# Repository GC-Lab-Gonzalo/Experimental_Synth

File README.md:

# Experimental Synth — Sintetizador de Madera

Sintetizador experimental de **GC Lab Chile**: una caja de madera con un teclado de 49 teclas reciclado de un Casio,
perillas, teclas mecánicas y LEDs RGB. Funciona con dos ESP32-S3 y tres placas de 180 × 75 mm diseñadas en KiCad 9.

| Placa | Qué hace |
|---|---|
| **Cerebro** | ESP32-S3, teclado (MCP23017), DAC PCM5102A, OLED, microSD, encoder EC11 y 8 LEDs WS2812B |
| **Control** | 8 perillas y 16 teclas leídas con 3 multiplexores CD74HC4051, más 16 LEDs WS2812B |
| **Placa 1** | Plantas y entorno: ESP32-S3, sensores ambientales, dos SHT40, radar HLK-LD2410C, DAC y pantalla |

## ⚠️ Fallos conocidos (corregidos en los archivos actuales)

**v6 → v6.1 (2026-11-24): huella de los LED WS2812B 6028 en espejo.**
En la revisión v6 de las placas **Cerebro** y **Control**, la huella del LED de montaje inverso
(`LED_WS2812B_6028_REV`) quedó en espejo respecto del componente real. GND y 5V caían en la diagonal equivocada,
así que el LED no calzaba en ninguna orientación. Afectó a los 24 LEDs.

- **Los archivos de este repositorio (v6.1) ya están corregidos.** La huella nueva `LED_WS2812B-6028_Inverso`
  (en `hardware/biblioteca/GCLab.pretty/`) se verificó contra la hoja de datos XINGLIGHT XL-6028RGBC-WS2812B
  (pág. 11, vista desde la lente) y contra la placa PercuSynth V2, que usa el mismo LED y funciona.
- La zona de los LED se re-ruteó en las dos placas. El DRC de KiCad da 0 errores y 0 conexiones pendientes,
  igual que antes. El orden de la cadena de LEDs no cambió, así que el firmware sirve tal cual.
- Cada LED tiene ahora un **triángulo de serigrafía junto al pad de GND**. La pata en punta del 6028
  (la de la esquina cortada) es GND. En la fila de abajo de la Control los LED van girados 180° respecto de
  los de arriba.
- **Si tienes placas v6 ya fabricadas:** suelda los LED mirando hacia atrás o corrige con puentes de cable
  esmaltado. No vuelvas a fabricar la v6: sus archivos no se publican aquí.

La Placa 1 no lleva estos LED y no cambió.

## Contenido

```
hardware/
  kicad/          Placas en KiCad 9 (cerebro_v6.1, control_v6.1, placa1_v4)
  fabricacion/    Un ZIP de Gerber + taladros por placa, listo para JLCPCB, y renders de frente y atrás
  biblioteca/     GCLab.pretty con la huella corregida del WS2812B 6028 inverso
firmware/         Sketches de Arduino para ESP32-S3 (pruebas por placa y los dos sintetizadores)
docs/
  PINOUT.md       Conexiones, pines del ESP32-S3, cable entre placas, teclado, LEDs y multiplexores
  montaje/        Diagramas de conexión del módulo MCP23017 con el teclado
```

## Fabricar

- Sube el ZIP de `hardware/fabricacion/<placa>/` tal cual. Son placas de 2 capas, de 180 × 75 mm.
- Las ventanas rectangulares de los LED son cortes de la placa (van en el contorno, capa Edge.Cuts).
- Compra el WS2812B 6028 en versión **de montaje inverso** («reverse mount»), por ejemplo el XINGLIGHT
  XL-6028RGBC-WS2812B. Uno común queda alumbrando hacia atrás.

## Antes de armar

- **5V del ESP32-S3 (Cerebro):** el DAC, los LEDs y el cable a la Control se alimentan del pin 5V del
  ESP32-S3-DevKitC-1. Muchas de esas placas traen ese pin desconectado hasta que se cierra un puente de soldadura
  (marcado IN-OUT o similar). Si nada de 5V prende, revisa ese puente.
- **Orientación del ESP32 en la Cerebro:** guíate por la serigrafía (pin 1 = 3V3). Para cables provisorios usa los
  pads rotulados de la placa (OLED, J3) y no cuentes pines del módulo.
- **Firmware de LEDs:** con el núcleo Arduino-ESP32 3.2.0, `Adafruit_NeoPixel` puede fallar al azar (los LED se
  apagan). `firmware/synth_ambiente_placa1/` maneja el RMT directo con la configuración en cero para evitarlo;
  `firmware/prueba_placa1/` todavía usa `Adafruit_NeoPixel`. Otra opción es usar el núcleo 3.3.x.
- Compila con «USB CDC On Boot: Enabled» y programa por el USB nativo del ESP32-S3.

## Licencia

Todo el contenido de este repositorio (placas, Gerber, huellas, firmware y documentación) está bajo la licencia
[Creative Commons Atribución-NoComercial-CompartirIgual 4.0 Internacional (CC BY-NC-SA 4.0)](LICENSE).

- **Puedes** usarlo, estudiarlo, modificarlo y fabricar placas para ti o para enseñar sin fines de lucro.
- **Debes** dar crédito a GC Lab Chile y enlazar este repositorio: `https://github.com/GC-Lab-Gonzalo/Experimental_Synth`.
- **No puedes** venderlo ni usarlo con fines comerciales (por ejemplo, vender placas, kits o instrumentos basados
  en este diseño, o cobrar talleres que lo usen) sin permiso escrito de GC Lab Chile.
- Si lo modificas y lo compartes, tiene que ser con esta misma licencia.

¿Te interesa un uso comercial? Escríbenos desde [gclabchile.com](https://www.gclabchile.com).

Copyright © 2026 GC Lab Chile.

---

Hecho en Chile por [GC Lab Chile](https://www.gclabchile.com): ingeniería electrónica, IA y artes creativas.

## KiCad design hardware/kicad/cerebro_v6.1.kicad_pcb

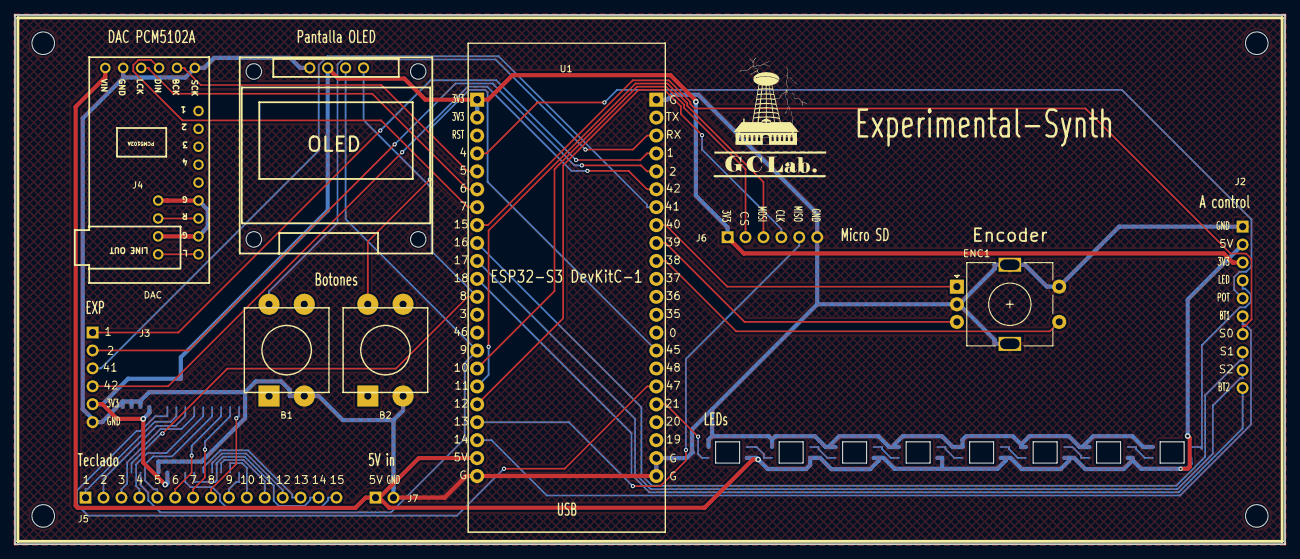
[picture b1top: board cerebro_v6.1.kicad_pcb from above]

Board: 2 copper layers, 180.0 x 75.0 mm, 26 parts (0 on the bottom side), 55 nets.

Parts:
B1, B2: TACT_12X12_PROTOSYNTH
C1: C0805
D1, D2, D3, D4, D5, D6, D7, D8: XL-6028RGBC-WS2812B; LED_WS2812B-6028_Inverso
DAC: PCM5102A
ENC1: EC11; RotaryEncoder_Alps_EC11E-Switch_Vertical_H20mm
Hole_gge700002: Hole_gge700002
Hole_gge700003: Hole_gge700003
Hole_gge700004: Hole_gge700004
Hole_gge700005: Hole_gge700005
J2: HDR_1X10
J3: HDR_1X6
J4: LINEOUT_1X4
J5: HDR_1X15
J6: MICROSD_3V3_1X6
J7: HDR_1X2
OLED: OLED-TH_OLED0.96-I2C
U1: ESP32-S3-DEVKITC-1
U3: SOIC28W_MCP23017

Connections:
3V3: C1.1, J2.3, J3.5, J6.1, OLED.4, U1.1, U1.2, U3.9, U3.18
5V: D1.3, D2.3, D3.3, D4.3, D5.3, D6.3, D7.3, D8.3, DAC.15, J2.2, J7.1, U1.21
AGND: DAC.6, DAC.8, J4.1, J4.3
BCK: DAC.11, U1.5
BL1: D1.4, D2.2
BL2: D2.4, D3.2
BL3: D3.4, D4.2
BL4: D4.4, D5.2
BL5: D5.4, D6.2
BL6: D6.4, D7.2
BL7: D7.4, D8.2
BTN_A: B1.1, U1.25
BTN_B: B2.1, U1.37
DIN: DAC.12, U1.7
ENC_A: ENC1.A, U1.30
ENC_B: ENC1.B, U1.31
ENC_SW: ENC1.S1, U1.32
EXP_G1: J3.1, U1.26
EXP_G2: J3.2, U1.27
EXP_G41: J3.3, U1.29
EXP_G42: J3.4, U1.28
GND: B1.3, B2.3, C1.2, D1.1, D2.1, D3.1, D4.1, D5.1, D6.1, D7.1, D8.1, DAC.10, DAC.14, ENC1.C, ENC1.MP, ENC1.S2, J2.1, J3.6, J6.6, J7.2, OLED.3, U1.22, U1.23, U1.43, U1.44, U3.10, U3.15, U3.16, U3.17
KB0: J5.1, U3.21
KB1: J5.2, U3.22
KB2: J5.3, U3.23
KB3: J5.4, U3.24
KB4: J5.5, U3.25
KB5: J5.6, U3.26
KB6: J5.7, U3.27
KB7: J5.8, U3.28
KB8: J5.9, U3.1
KB9: J5.10, U3.2
KB10: J5.11, U3.3
KB11: J5.12, U3.4
KB12: J5.13, U3.5
KB13: J5.14, U3.6
KB14: J5.15, U3.7
KB_INT: U1.39, U3.20
LCK: DAC.13, U1.6
LED_DIN: D1.2, U1.40
LED_OUT: D8.4, J2.4
LOUT: DAC.9, J4.4
ROUT: DAC.7, J4.2
S0: J2.7, U1.8
S1: J2.8, U1.9
S2: J2.9, U1.10
SCL: OLED.5, U1.15, U3.12
SDA: OLED.6, U1.12, U3.13
SD_CS: J6.2, U1.16
SD_MISO: J6.5, U1.19
SD_MOSI: J6.3, U1.17
SD_SCK: J6.4, U1.18
SIG_BTN1: J2.6, U1.20
SIG_BTN2: J2.10, U1.11
SIG_POT: J2.5, U1.4

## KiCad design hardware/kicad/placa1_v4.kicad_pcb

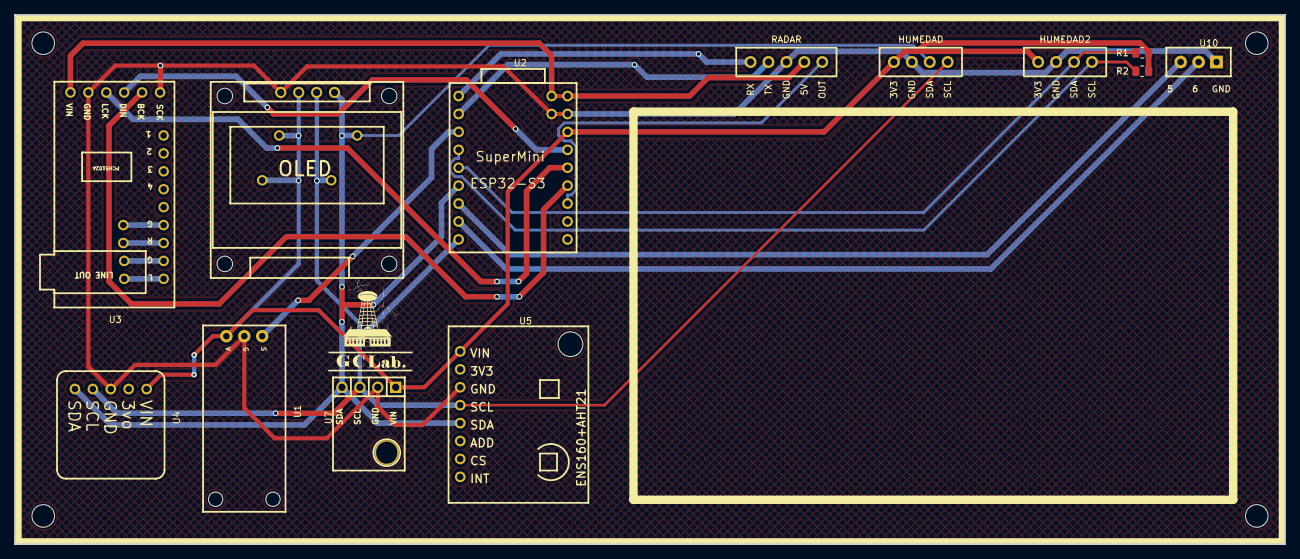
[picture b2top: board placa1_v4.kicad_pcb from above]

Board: 2 copper layers, 180.0 x 75.0 mm, 27 parts (0 on the bottom side), 20 nets.

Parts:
HUMEDAD, HUMEDAD2: SHT40; PinHeader_1x04_P2.54mm_Vertical
Hole_gge28341: Hole_gge28341
Hole_gge28356: Hole_gge28356
Hole_gge28371: Hole_gge28371
Hole_gge28386: Hole_gge28386
OLED: OLED-TH_OLED0.96-I2C
Pad_gge45666: Pad_gge45666
Pad_gge45693: Pad_gge45693
Pad_gge49285: Pad_gge49285
Pad_gge49315: Pad_gge49315
Pad_gge49345: Pad_gge49345
Pad_gge49375: Pad_gge49375
Pad_gge49585: Pad_gge49585
Pad_gge49612: Pad_gge49612
Pad_gge49666: Pad_gge49666
Pad_gge49791: Pad_gge49791
R1, R2: 4k7; R_0805_2012Metric
RADAR: HLK-LD2410C; PinHeader_1x05_P2.54mm_Vertical
U1: GUVA-S12SD_MODULE
U2: ESP32_S3_SUPERMINI_MINIMAL
U3: PCM5102A
U4: VEML7700_FOOTPRINT
U5: ENS160+AHT21
U7: BMP180
U10: HEADER3X1

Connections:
BCK: U2.13, U3.11
CINCO: Pad_gge45666.1, RADAR.4, U2.18, U3.15
DIN: U2.15, U3.12
GG: Pad_gge49285.3, U3.6
GGG: Pad_gge49345.5, U3.8
GND: HUMEDAD.2, HUMEDAD2.2, OLED.3, Pad_gge45693.2, RADAR.3, U1.2, U2.17, U3.10, U3.14, U4.3, U5.GND, U7.2, U10.3
GUVA: U1.3, U2.3
LCK: U2.14, U3.13
LL: Pad_gge49375.6, U3.9
RADAR_OUT: RADAR.5, U2.12
RR: Pad_gge49315.4, U3.7
RX: RADAR.1, U2.1
S$48961: U2.7, U10.1
S$48965: U2.8, U10.2
SCL: HUMEDAD.4, OLED.5, Pad_gge49585.7, U2.9, U4.4, U5.SCL, U7.3
SCL2: HUMEDAD2.4, R2.1, U2.4
SDA: HUMEDAD.3, OLED.6, Pad_gge49666.9, U2.6, U4.5, U5.SDA, U7.4
SDA2: HUMEDAD2.3, R1.1, U2.5
TX: RADAR.2, U2.2
VIN: HUMEDAD.1, HUMEDAD2.1, OLED.4, Pad_gge49612.8, Pad_gge49791.10, R1.2, R2.2, U1.1, U2.16, U4.1, U5.VIN, U7.1

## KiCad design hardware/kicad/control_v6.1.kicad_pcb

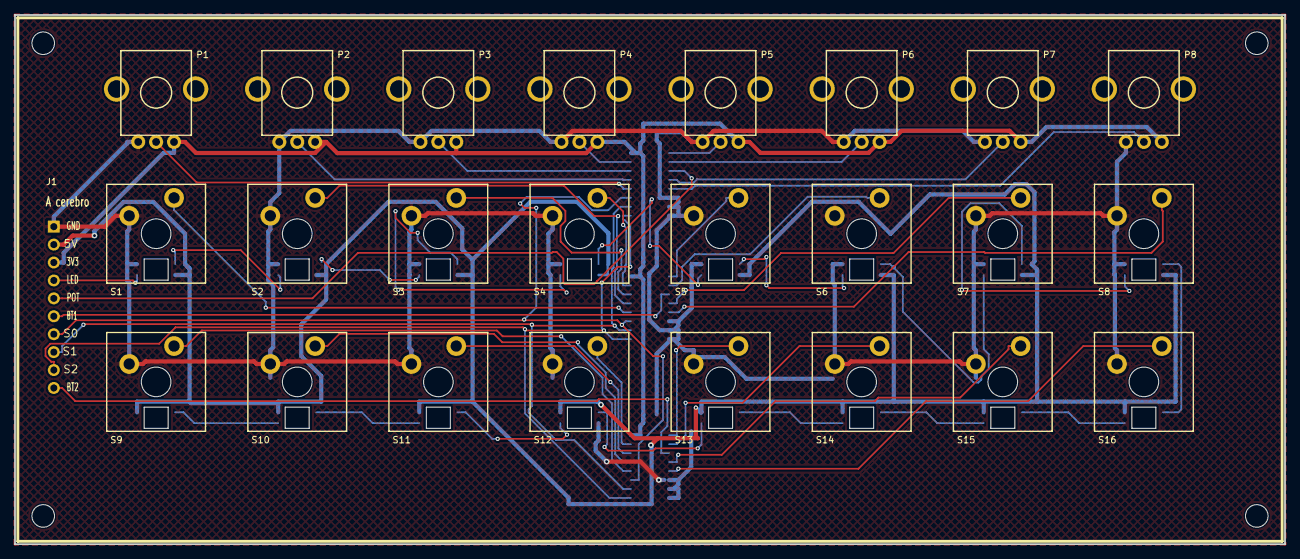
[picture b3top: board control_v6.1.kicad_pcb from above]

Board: 2 copper layers, 180.0 x 75.0 mm, 51 parts (0 on the bottom side), 49 nets.

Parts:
C1, C2, C3: C0805
D1, D2, D3, D4, D5, D6, D7, D8, D9, D10, D11, D12, D13, D14, D15, D16: XL-6028RGBC-WS2812B; LED_WS2812B-6028_Inverso
Hole_gge700423: Hole_gge700423
Hole_gge700424: Hole_gge700424
Hole_gge700425: Hole_gge700425
Hole_gge700426: Hole_gge700426
J1: HDR_1X10
P1, P2, P3, P4, P5, P6, P7, P8: POT_R09V_PERCUSYNTH
S1, S2, S3, S4, S5, S6, S7, S8, S9, S10, S11, S12, S13, S14, S15, S16: SW_MX_PERCUSYNTH
U1, U2, U3: SOIC16_CD74HC4051

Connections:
3V3: C1.1, C2.1, C3.1, J1.3, P1.3, P2.3, P3.3, P4.3, P5.3, P6.3, P7.3, P8.3, U1.16, U2.16, U3.16
5V: D1.3, D2.3, D3.3, D4.3, D5.3, D6.3, D7.3, D8.3, D9.3, D10.3, D11.3, D12.3, D13.3, D14.3, D15.3, D16.3, J1.2
BTN1: S1.2, U2.12
BTN2: S2.2, U2.13
BTN3: S3.2, U2.14
BTN4: S4.2, U2.15
BTN5: S5.2, U2.1
BTN6: S6.2, U2.2
BTN7: S7.2, U2.4
BTN8: S8.2, U2.5
BTN9: S9.2, U3.12
BTN10: S10.2, U3.13
BTN11: S11.2, U3.14
BTN12: S12.2, U3.15
BTN13: S13.2, U3.1
BTN14: S14.2, U3.2
BTN15: S15.2, U3.4
BTN16: S16.2, U3.5
GND: C1.2, C2.2, C3.2, D1.1, D2.1, D3.1, D4.1, D5.1, D6.1, D7.1, D8.1, D9.1, D10.1, D11.1, D12.1, D13.1, D14.1, D15.1, D16.1, J1.1, P1.1, P2.1, P3.1, P4.1, P5.1, P6.1, P7.1, P8.1, S1.1, S2.1, S3.1, S4.1, S5.1, S6.1, S7.1, S8.1, S9.1, S10.1, S11.1, S12.1, S13.1, S14.1, S15.1, S16.1, U1.6, U1.7, U1.8, U2.6, U2.7, U2.8, U3.6, U3.7, U3.8
LD1: D1.4, D2.2
LD2: D2.4, D3.2
LD3: D3.4, D4.2
LD4: D4.4, D5.2
LD5: D5.4, D6.2
LD6: D6.4, D7.2
LD7: D7.4, D8.2
LD8: D8.4, D9.2
LD9: D9.4, D10.2
LD10: D10.4, D11.2
LD11: D11.4, D12.2
LD12: D12.4, D13.2
LD13: D13.4, D14.2
LD14: D14.4, D15.2
LD15: D15.4, D16.2
LED_DIN: D1.2, J1.4
POT1: P1.2, U1.12
POT2: P2.2, U1.13
POT3: P3.2, U1.14
POT4: P4.2, U1.15
POT5: P5.2, U1.1
POT6: P6.2, U1.2
POT7: P7.2, U1.4
POT8: P8.2, U1.5
S0: J1.7, U1.11, U2.11, U3.11
S1: J1.8, U1.10, U2.10, U3.10
S2: J1.9, U1.9, U2.9, U3.9
SIG_BTN1: J1.6, U2.3
SIG_BTN2: J1.10, U3.3
SIG_POT: J1.5, U1.3

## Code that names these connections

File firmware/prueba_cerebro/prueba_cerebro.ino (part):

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// ---- Pines (sacados de la placa en KiCad) ----
#define PIN_SDA   8
#define PIN_SCL   9
#define ENC_A     40
#define ENC_B     39
#define ENC_SW    38
#define BTN_1     44
#define BTN_2     45     // pin de arranque: solo pull-up interna, después de arrancar
#define I2S_BCK   5
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  Serial.printf("Teclado %s (cable 1 en %s)\n", TECLADO_INVERTIDO ? "INVERTIDO" : "normal",
                TECLADO_INVERTIDO ? "B6" : "A0");

  pinMode(ENC_A, INPUT_PULLUP);
  pinMode(ENC_B, INPUT_PULLUP);
  pinMode(ENC_SW, INPUT_PULLUP);
  pinMode(BTN_1, INPUT_PULLUP);
  pinMode(BTN_2, INPUT_PULLUP);
  encEstado = (digitalRead(ENC_A) << 1) | digitalRead(ENC_B);
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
